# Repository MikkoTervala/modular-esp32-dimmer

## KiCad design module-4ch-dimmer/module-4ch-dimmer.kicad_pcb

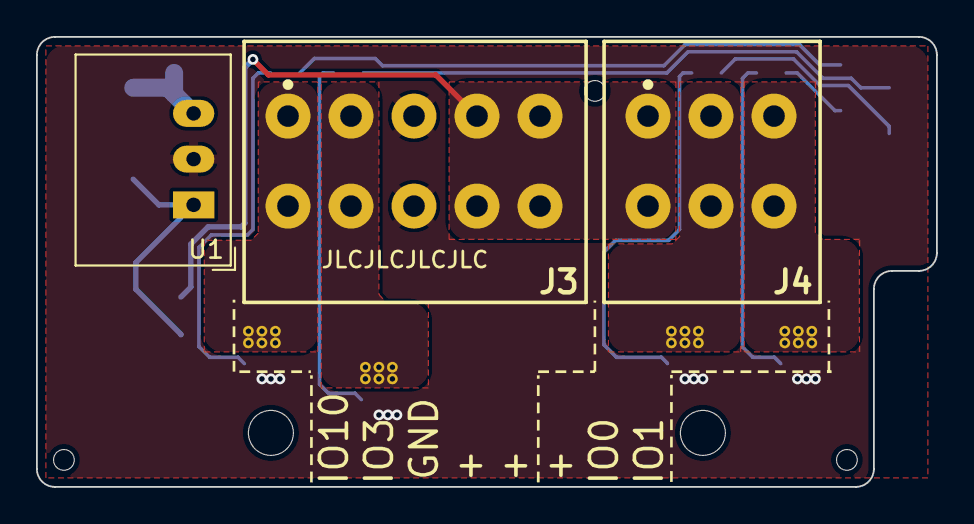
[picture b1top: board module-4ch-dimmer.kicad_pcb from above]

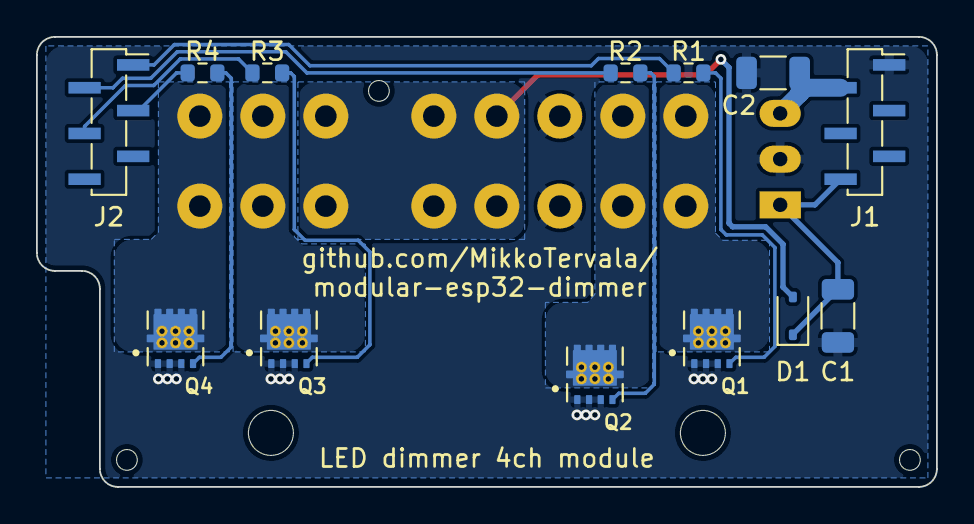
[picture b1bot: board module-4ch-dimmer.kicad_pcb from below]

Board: 2 copper layers, 50.0 x 25.0 mm, 21 parts (13 on the bottom side), 16 nets.

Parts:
C1, C2: 10µf; C_1206_3216Metric
D1: 1N5819WS 1A 40V; D_SOD-323
H1, H2: MountingHole-Spacer; MountingHole_2.5mm
H3, H4, H5: JLCPCB tooling hole
J1, J2: Conn_01x06_Socket; PinSocket_1x06_P1.27mm_Vertical_SMD_Pin1Right
J3: Conn_01x05; CONN_2601-1105_Wago
J4: Conn_01x03; CONN_2601-1103_Wago
Q1, Q2, Q3, Q4: AON7524; TRANS_AON7403
R1, R2, R3, R4: 100; R_0603_1608Metric
U1: R-78E3.3-0.5; Converter_DCDC_RECOM_R-78E-0.5_THT

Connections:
+3V3: C2.2, J1.2, U1.3 (OUT)
+12C: C1.2, D1.1 (K), J1.6, U1.1 (IN)
+12V: D1.2 (A), J3.4, J3.5, J4.1
/CH1: J3.1, Q1.2 (D)
/CH2: J3.2, Q2.2 (D)
/CH3: J4.2, Q3.2 (D)
/CH4: J4.3, Q4.2 (D)
GND: C1.1, C2.1, J1.1, J3.3, Q1.3 (S), Q2.3 (S), Q3.3 (S), Q4.3 (S), U1.2 (GND)
GPIO0: J2.4, R3.1
GPIO1: J2.3, R4.1
GPIO3: J2.2, R2.1
GPIO10: J2.1, R1.1
unnamed: Q1.1 (G), R1.2
unnamed: Q2.1 (G), R2.2
unnamed: Q3.1 (G), R3.2
unnamed: Q4.1 (G), R4.2

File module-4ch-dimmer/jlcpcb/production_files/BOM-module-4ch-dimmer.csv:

Comment,Designator,Footprint,LCSC
10µf,"C1,C2",C_1206_3216Metric,C13585
1N5819WS 1A 40V,D1,D_SOD-323,C191023
100,"R1,R2,R3,R4",R_0603_1608Metric,C22775
Conn_01x06_Socket,"J1,J2",PinSocket_1x06_P1.27mm_Vertical_SMD_Pin1Right,C2881496
AON7524,"Q1,Q2,Q3,Q4",TRANS_AON7403,C431195

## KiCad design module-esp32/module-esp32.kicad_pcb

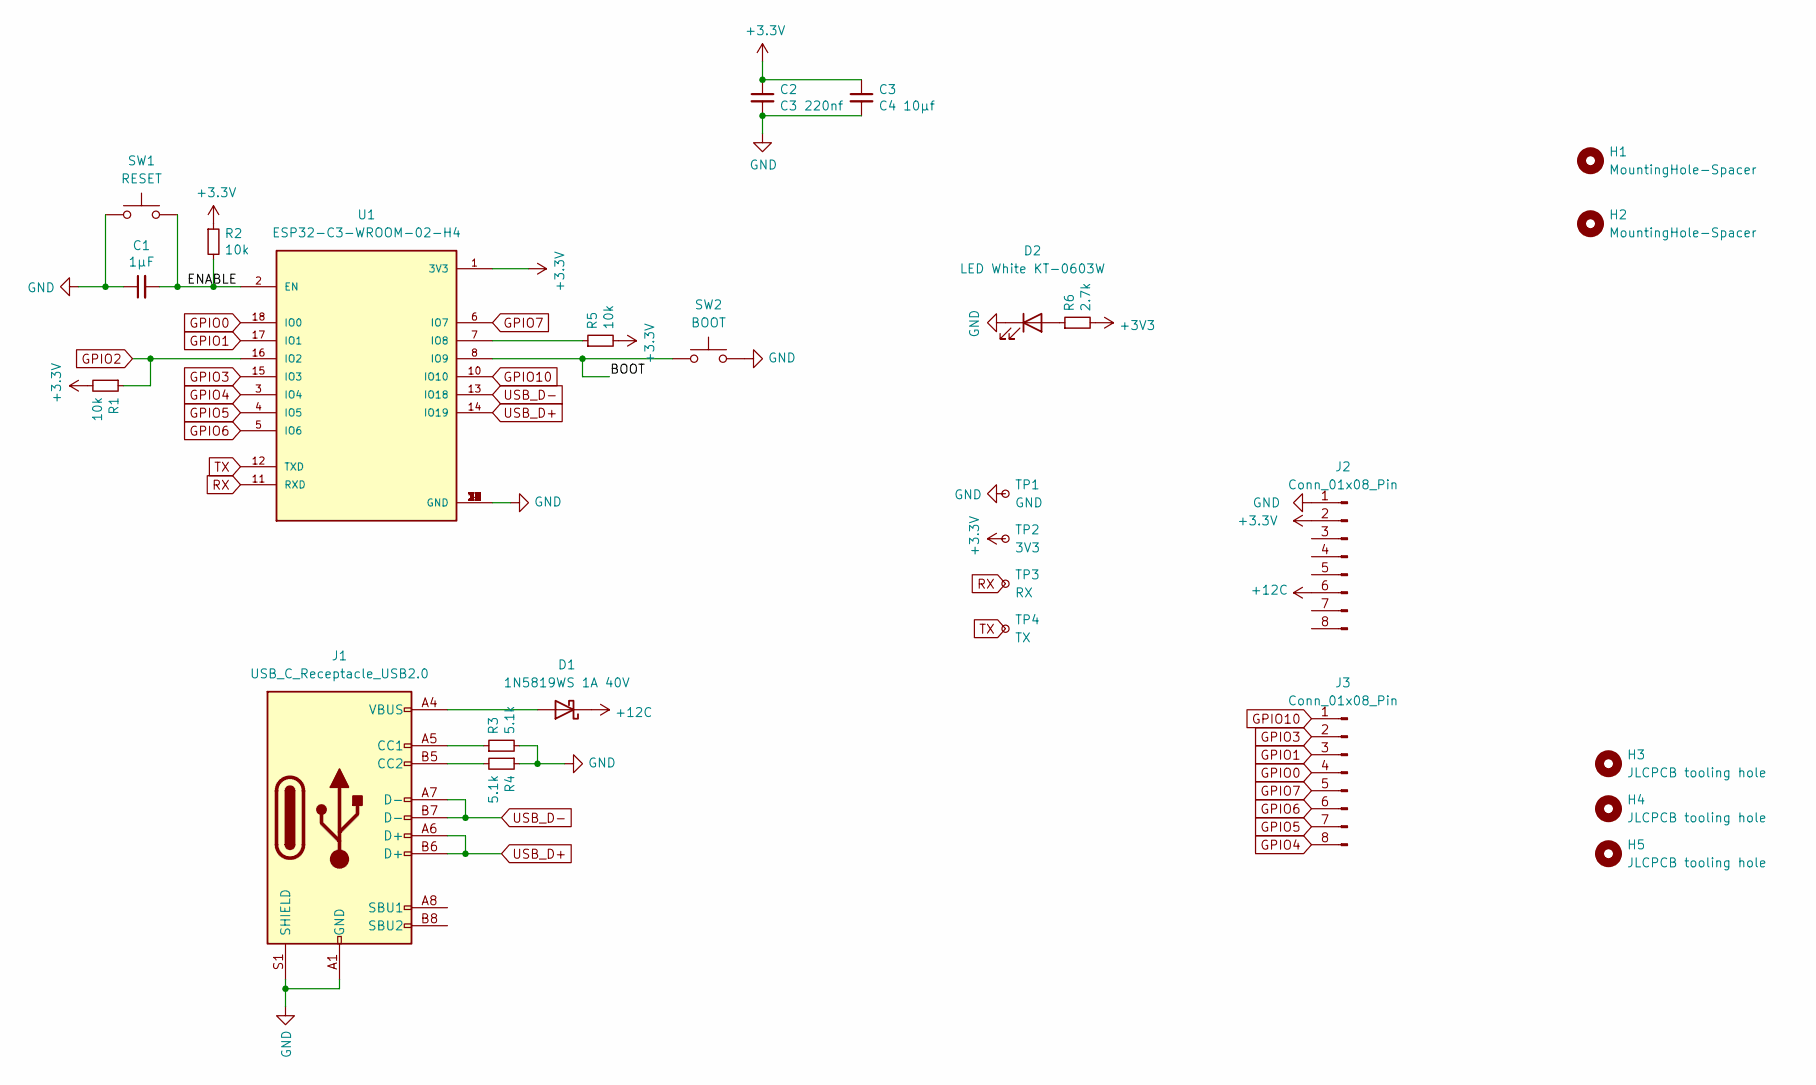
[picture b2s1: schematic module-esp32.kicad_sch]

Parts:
C1: 1µF; C_0603_1608Metric; LCSC Part # C15849
C2: C3 220nf; C_0603_1608Metric; LCSC Part # C21120
C3: C4 10µf; C_1206_3216Metric; LCSC Part # C13585
D1: 1N5819WS 1A 40V; D_SOD-323; LCSC Part # C191023
D2: LED White KT-0603W; LED_0603_1608Metric; LCSC Part # C2290
H1, H2: MountingHole-Spacer; MountingHole_2.5mm
H3, H4, H5: JLCPCB tooling hole
J1: USB_C_Receptacle_USB2.0; CONN_TYPE-C-31-M-12; LCSC Part # C165948
J2, J3: Conn_01x08_Pin; PinHeader_1x08_P1.27mm_Vertical_SMD_Pin1Right; LCSC Part # C5243492
R1, R2, R5: 10k; R_0603_1608Metric; LCSC Part # C25804
R3, R4: 5.1k; R_0603_1608Metric; LCSC Part # C23186
R6: 2.7k; R_0603_1608Metric; LCSC Part # C13167
SW1: RESET; SW_SPST_PTS810; LCSC Part # C139797
SW2: BOOT; SW_SPST_PTS810; LCSC Part # C139797
TP1: GND; TestPoint_Pad_D1.0mm
TP2: 3V3; TestPoint_Pad_D1.0mm
TP3: RX; TestPoint_Pad_D1.0mm
TP4: TX; TestPoint_Pad_D1.0mm
U1: ESP32-C3-WROOM-02-H4; MODULE_ESP32-C3-WROOM-02-H4; LCSC Part # C2934560

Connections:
+12C: D1.1 (K), J2.6
/BOOT: SW2.1, U1.8 (IO9)
/ENABLE: C1.2, R2.2, SW1.2, U1.2 (EN)
GND: C1.1, C2.2, C3.2, D2.1 (K), J1.A1 (GND), J1.A12 (GND), J1.B1 (GND), J1.B12 (GND), J1.S1 (SHIELD), J2.1, R3.2, R4.1, SW1.1, SW2.2, TP1.1, U1.9 (GND), U1.19 (GND), U1.20 (GND), U1.21 (GND), U1.22 (GND), U1.23 (GND), U1.24 (GND), U1.25 (GND), U1.26 (GND), U1.27 (GND), U1.28 (GND), U1.29 (GND), U1.30 (GND), U1.31 (GND), U1.32 (GND), U1.33 (GND), U1.34 (GND), U1.35 (GND), U1.36 (GND), U1.37 (GND), U1.38 (GND), U1.39 (GND)
GPIO0: J3.4, U1.18 (IO0)
GPIO1: J3.3, U1.17 (IO1)
GPIO2: R1.1, U1.16 (IO2)
GPIO3: J3.2, U1.15 (IO3)
GPIO4: J3.8, U1.3 (IO4)
GPIO5: J3.7, U1.4 (IO5)
GPIO6: J3.6, U1.5 (IO6)
GPIO7: J3.5, U1.6 (IO7)
GPIO10: J3.1, U1.10 (IO10)
unnamed: D1.2 (A), J1.A4 (VBUS), J1.A9 (VBUS), J1.B4 (VBUS), J1.B9 (VBUS)
unnamed: D2.2 (A), R6.1
unnamed: J1.A5 (CC1), R3.1
unnamed: J1.B5 (CC2), R4.2
unnamed: R5.1, U1.7 (IO8)
RX: TP3.1, U1.11 (RXD)
TX: TP4.1, U1.12 (TXD)
USB_D+: J1.A6 (D+), J1.B6 (D+), U1.14 (IO19)
USB_D-: J1.A7 (D-), J1.B7 (D-), U1.13 (IO18)

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
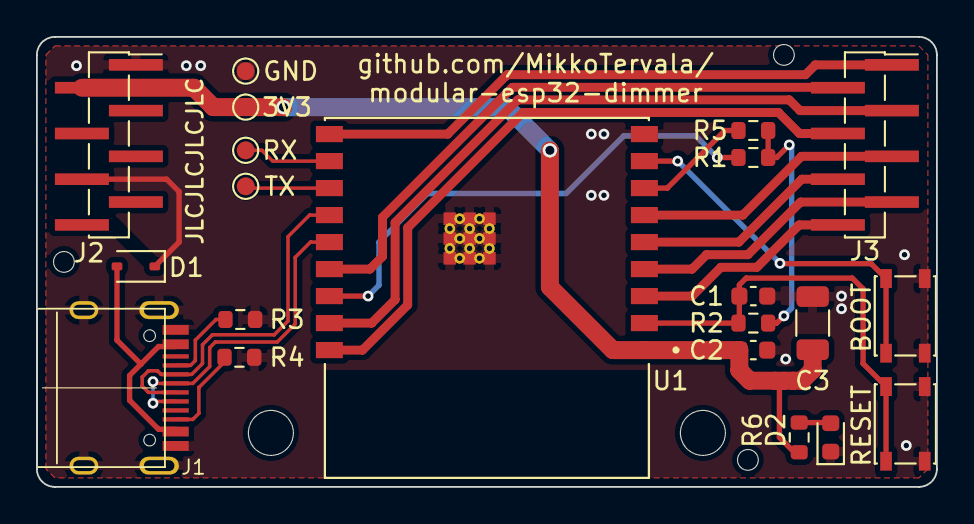
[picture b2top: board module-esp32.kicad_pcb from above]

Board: 2 copper layers, 50.0 x 25.0 mm, 26 parts (0 on the bottom side), 23 nets.

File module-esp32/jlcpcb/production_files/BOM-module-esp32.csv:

Comment,Designator,Footprint,LCSC
2.7k,R6,R_0603_1608Metric,C13167
C4 10µf,C3,C_1206_3216Metric,C13585
RESET,"SW1,SW2",SW_SPST_PTS810,C139797
1µF,C1,C_0603_1608Metric,C15849
USB_C_Receptacle_USB2.0,J1,CONN_TYPE-C-31-M-12,C165948
1N5819WS 1A 40V,D1,D_SOD-323,C191023
C3 220nf,C2,C_0603_1608Metric,C21120
LED White KT-0603W,D2,LED_0603_1608Metric,C2290
5.1k,"R3,R4",R_0603_1608Metric,C23186
10k,"R1,R2,R5",R_0603_1608Metric,C25804
ESP32-C3-WROOM-02-H4,U1,MODULE_ESP32-C3-WROOM-02-H4,C2934560
Conn_01x08_Pin,"J2,J3",PinHeader_1x08_P1.27mm_Vertical_SMD_Pin1Right,C5243492

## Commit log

2023-11-27 First commit production version
